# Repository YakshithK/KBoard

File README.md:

# KBoard

An 84-key custom mechanical keyboard built from scratch around the RP2040. No dev module: the RP2040, flash, regulator, USB-C, crystal, and support circuitry are all on the board. Uses Cherry MX Browns.

| Top | Bottom |
| --- | --- |
|  |  |

## Features
- 84 hot-swap MX-compatible switches in a ROW2COL matrix with per-key diodes
- From-scratch RP2040 design with USB-C, 16Mbit flash, and onboard 3.3V regulation
- QMK firmware with RP2040 USB bootloader (drag-and-drop UF2 flashing)

## Technical Details

The PCB is a basic 2-layer pcb (306 x 125 mm) using an RP2040 SoC with a USB-C connector. There's also a switch broken on the bottom for boot/reset.

## Bill of Materials

Please see: [`BOM.csv`](BOM.csv)

## Repo Index

### Start Here

| Path | Purpose |
| --- | --- |
| [`README.md`](README.md) | Project overview, features, bill of materials, and this repository map |
| [`BOM.csv`](BOM.csv) | Bill of materials |

### Hardware: KiCad

| Path | Purpose |
| --- | --- |
| [`kboard_pcb/KBoard.kicad_pro`](kboard_pcb/KBoard.kicad_pro) | KiCad project settings |
| [`kboard_pcb/KBoard.kicad_sch`](kboard_pcb/KBoard.kicad_sch) | Source schematic |
| [`kboard_pcb/KBoard.kicad_pcb`](kboard_pcb/KBoard.kicad_pcb) | Source PCB layout |

### Hardware: CAD Files

| Path | Purpose |
| --- | --- |
| [`CAD/KBoard.step`](CAD/KBoard.step) | 3D CAD model in STEP format |
| [`PCB/KBoard.step`](PCB/KBoard.step) | 3D CAD model in STEP format |
| [`PCB/KBoard.stl`](PCB/KBoard.stl) | 3D CAD model in STL format (local only, too large for git) |

### Hardware: Production Files

| Path | Purpose |
| --- | --- |
| [`production/KBoard-gerbers.zip`](production/KBoard-gerbers.zip) | Zipped Gerbers + drill, ready to upload to the fab |
| [`production/KBoard.step`](production/KBoard.step) | STEP model bundled for fabrication |
| [`production/gerbers/`](production/gerbers/) | Gerber plot, drill, and pick-and-place files |
| [`production/firmware/`](production/firmware/) | QMK firmware source and built UF2 for flashing |

### Hardware: Visual References

| Path | Purpose |
| --- | --- |
| [`assets/schematic.svg`](assets/schematic.svg) | Schematic preview |
| [`assets/pcb-top.png`](assets/pcb-top.png) | Top-side PCB render |
| [`assets/pcb-bottom.png`](assets/pcb-bottom.png) | Bottom-side PCB render |

### Firmware: QMK

| Path | Purpose |
| --- | --- |
| [`firmware/kboard/keyboard.json`](firmware/kboard/keyboard.json) | Keyboard identity, RP2040 target, pins, matrix, and layout |
| [`firmware/kboard/rules.mk`](firmware/kboard/rules.mk) | QMK build settings |
| [`firmware/kboard/config.h`](firmware/kboard/config.h) | Board configuration |
| [`firmware/kboard/kboard.h`](firmware/kboard/kboard.h) | Keyboard header included by QMK |
| [`firmware/kboard/keymaps/default/keymap.c`](firmware/kboard/keymaps/default/keymap.c) | Default keymap |

Build the firmware with `qmk compile -kb kboard -km default` (the `firmware/kboard` folder must be linked or copied to `qmk_firmware/keyboards/kboard`). Flash the resulting UF2, also bundled at [`production/firmware/kboard_default.uf2`](production/firmware/kboard_default.uf2), by double-pressing reset and dragging it onto the USB drive.

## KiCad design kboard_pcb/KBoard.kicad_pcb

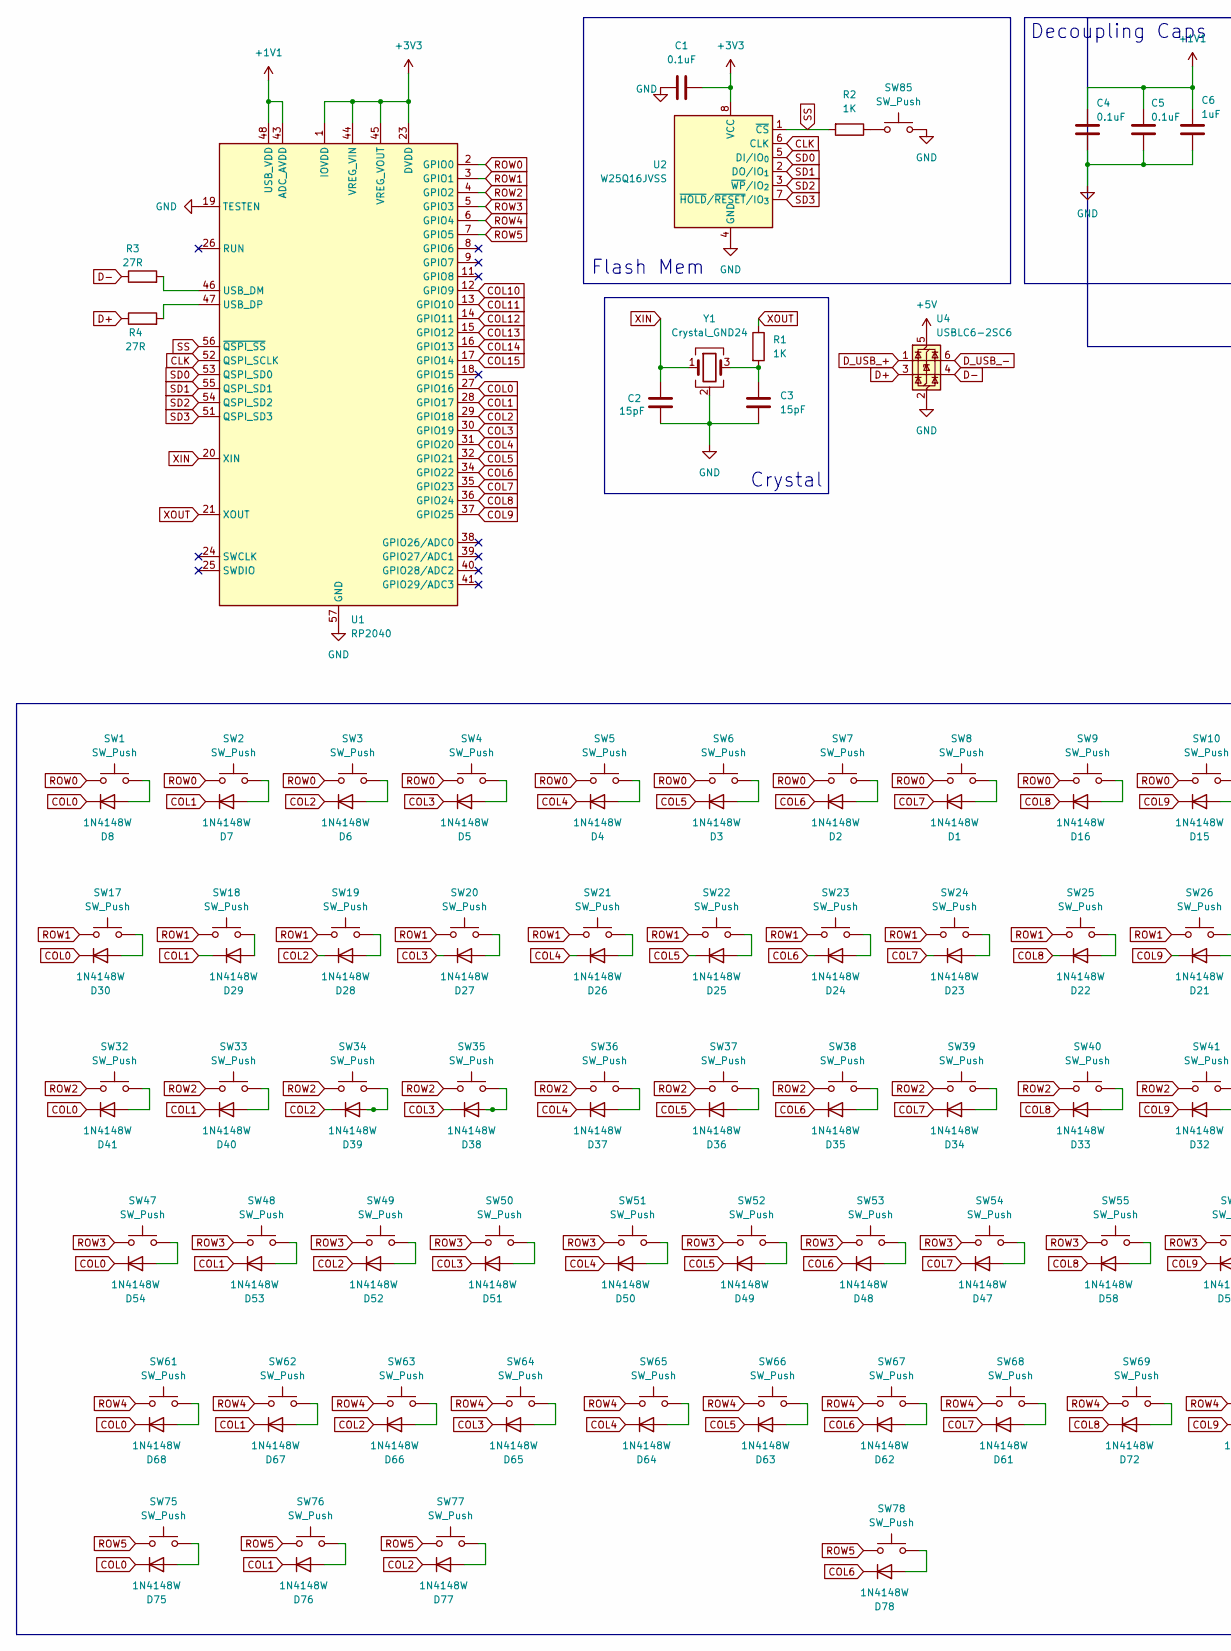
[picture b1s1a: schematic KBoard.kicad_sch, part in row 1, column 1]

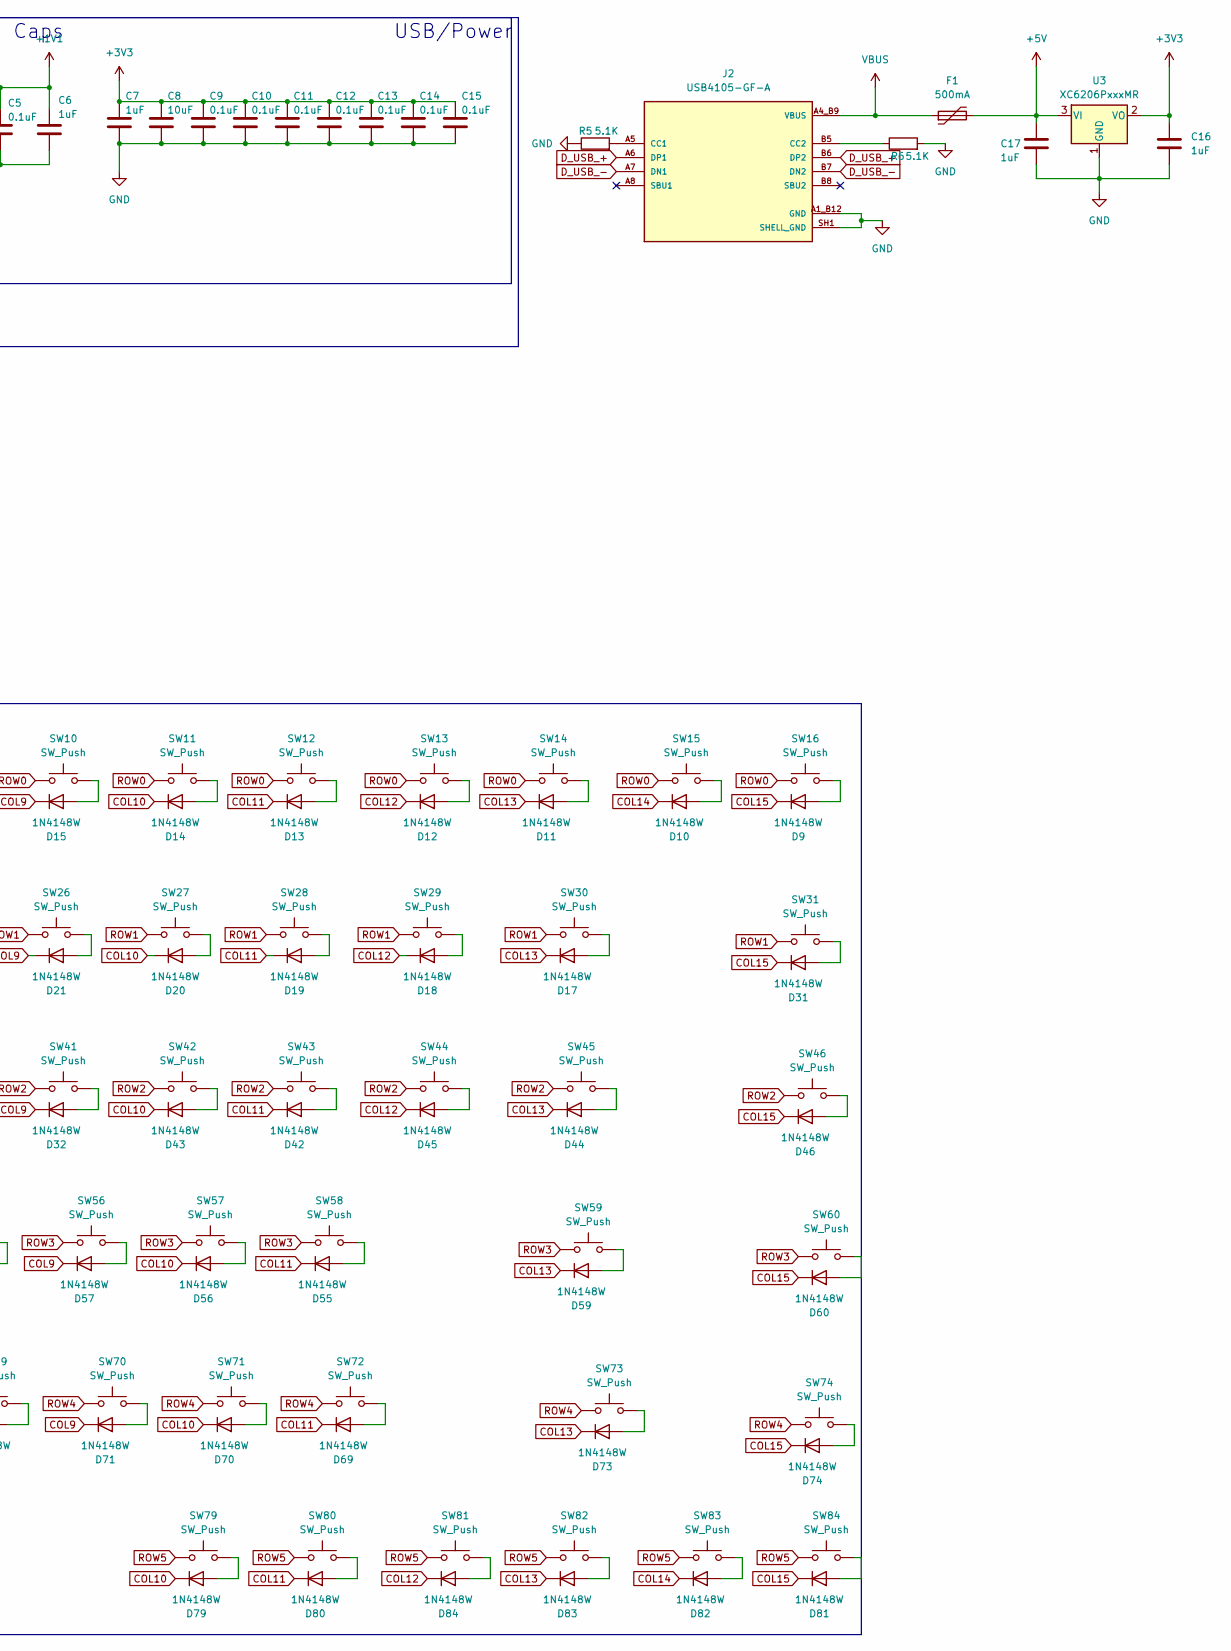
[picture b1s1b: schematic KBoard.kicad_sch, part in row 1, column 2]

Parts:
C1, C4, C5, C9, C10, C11, C12, C13, C14, C15: 0.1uF; C_0402_1005Metric
C2, C3: 15pF; C_0402_1005Metric
C6, C7, C16, C17: 1uF; C_0603_1608Metric
C8: 10uF; C_0603_1608Metric
D1, D2, D3, D4, D5, D6, D7, D8, D9, D10, D11, D12, D13, D14, D15, D16, D17, D18, D19, D20, D21, D22, D23, D24, D25, D26, D27, D28, D29, D30, D31, D32, D33, D34, D35, D36, D37, D38, D39, D40, D41, D42, D43, D44, D45, D46, D47, D48, D49, D50, D51, D52, D53, D54, D55, D56, D57, D58, D59, D60, D61, D62, D63, D64, D65, D66, D67, D68, D69, D70, D71, D72, D73, D74, D75, D76, D77, D78, D79, D80, D81, D82, D83, D84: 1N4148W; D_SOD-123
F1: 500mA; Fuse_0402_1005Metric
J2: USB4105-GF-A; GCT_USB4105-GF-A; PARTREV B4; DigiKey_Part_Number 2073-USB4105-GF-ACT-ND
R1, R2: 1K; C_0402_1005Metric
R3, R4: 27R; C_0402_1005Metric
R5, R6: 5.1K; C_0402_1005Metric
SW1, SW2, SW3, SW4, SW5, SW6, SW7, SW8, SW9, SW10, SW11, SW12, SW13, SW14, SW15, SW16, SW17, SW18, SW19, SW20, SW21, SW22, SW23, SW24, SW25, SW26, SW27, SW28, SW29, SW30, SW31, SW32, SW33, SW34, SW35, SW36, SW37, SW38, SW39, SW40, SW41, SW42, SW43, SW44, SW45, SW46, SW47, SW48, SW49, SW50, SW51, SW52, SW53, SW54, SW55, SW56, SW57, SW58, SW59, SW60, SW61, SW62, SW63, SW64, SW65, SW66, SW67, SW68, SW69, SW70, SW71, SW72, SW73, SW74, SW75, SW76, SW77, SW78, SW79, SW80, SW81, SW82, SW83, SW84: SW_Push; SW_MX_HS_CPG151101S11_1u
SW85: SW_Push; SW_SPST_CK_RS282G05A3
U1: RP2040; QFN-56-1EP_7x7mm_P0.4mm_EP3.2x3.2mm
U2: W25Q16JVSS; SOIC-8_5.3x5.3mm_P1.27mm
U3: XC6206PxxxMR; SOT-23-3
U4: USBLC6-2SC6; SOT-23-6
Y1: Crystal_GND24; Crystal_SMD_3225-4Pin_3.2x2.5mm

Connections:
+1V1: C4.1, C5.1, C6.1, U1.43 (ADC_AVDD), U1.48 (USB_VDD)
+3V3: C1.2, C7.1, C8.1, C9.1, C10.1, C11.1, C12.1, C13.1, C14.1, C15.1, C16.1, U1.1 (IOVDD), U1.10 (IOVDD), U1.22 (IOVDD), U1.23 (DVDD), U1.33 (IOVDD), U1.42 (IOVDD), U1.44 (VREG_VIN), U1.45 (VREG_VOUT), U1.49 (IOVDD), U1.50 (DVDD), U2.8 (VCC), U3.2 (VO)
+5V: C17.1, F1.2, U3.3 (VI), U4.5 (VBUS)
CLK: U1.52 (QSPI_SCLK), U2.6 (CLK)
COL0: D8.1 (K), D30.1 (K), D41.1 (K), D54.1 (K), D68.1 (K), D75.1 (K), U1.27 (GPIO16)
COL1: D7.1 (K), D29.1 (K), D40.1 (K), D53.1 (K), D67.1 (K), D76.1 (K), U1.28 (GPIO17)
COL2: D6.1 (K), D28.1 (K), D39.1 (K), D52.1 (K), D66.1 (K), D77.1 (K), U1.29 (GPIO18)
COL3: D5.1 (K), D27.1 (K), D38.1 (K), D51.1 (K), D65.1 (K), U1.30 (GPIO19)
COL4: D4.1 (K), D26.1 (K), D37.1 (K), D50.1 (K), D64.1 (K), U1.31 (GPIO20)
COL5: D3.1 (K), D25.1 (K), D36.1 (K), D49.1 (K), D63.1 (K), U1.32 (GPIO21)
COL6: D2.1 (K), D24.1 (K), D35.1 (K), D48.1 (K), D62.1 (K), D78.1 (K), U1.34 (GPIO22)
COL7: D1.1 (K), D23.1 (K), D34.1 (K), D47.1 (K), D61.1 (K), U1.35 (GPIO23)
COL8: D16.1 (K), D22.1 (K), D33.1 (K), D58.1 (K), D72.1 (K), U1.36 (GPIO24)
COL9: D15.1 (K), D21.1 (K), D32.1 (K), D57.1 (K), D71.1 (K), U1.37 (GPIO25)
COL10: D14.1 (K), D20.1 (K), D43.1 (K), D56.1 (K), D70.1 (K), D79.1 (K), U1.12 (GPIO9)
COL11: D13.1 (K), D19.1 (K), D42.1 (K), D55.1 (K), D69.1 (K), D80.1 (K), U1.13 (GPIO10)
COL12: D12.1 (K), D18.1 (K), D45.1 (K), D84.1 (K), U1.14 (GPIO11)
COL13: D11.1 (K), D17.1 (K), D44.1 (K), D59.1 (K), D73.1 (K), D83.1 (K), U1.15 (GPIO12)
COL14: D10.1 (K), D82.1 (K), U1.16 (GPIO13)
COL15: D9.1 (K), D31.1 (K), D46.1 (K), D60.1 (K), D74.1 (K), D81.1 (K), U1.17 (GPIO14)
D+: R4.1, U4.3 (I/O2)
D-: R3.1, U4.4 (I/O2)
D_USB_+: J2.A6 (DP1), J2.B6 (DP2), U4.1 (I/O1)
D_USB_-: J2.A7 (DN1), J2.B7 (DN2), U4.6 (I/O1)
GND: C1.1, C2.2, C3.2, C4.2, C5.2, C6.2, C7.2, C8.2, C9.2, C10.2, C11.2, C12.2, C13.2, C14.2, C15.2, C16.2, C17.2, J2.A1_B12 (GND), J2.B1_A12 (GND), J2.SH1 (SHELL_GND), J2.SH2 (SHELL_GND), J2.SH3 (SHELL_GND), J2.SH4 (SHELL_GND), R5.1, R6.2, SW85.2, U1.19 (TESTEN), U1.57 (GND), U2.4 (GND), U3.1 (GND), U4.2 (GND), Y1.2 (G), Y1.4 (G)
unnamed: C3.1, R1.2, Y1.3
unnamed: D1.2 (A), SW8.2
unnamed: D2.2 (A), SW7.2
unnamed: D3.2 (A), SW6.2
unnamed: D4.2 (A), SW5.2
unnamed: D5.2 (A), SW4.2
unnamed: D6.2 (A), SW3.2
unnamed: D7.2 (A), SW2.2
unnamed: D8.2 (A), SW1.2
unnamed: D9.2 (A), SW16.2
unnamed: D10.2 (A), SW15.2
unnamed: D11.2 (A), SW14.2
unnamed: D12.2 (A), SW13.2
unnamed: D13.2 (A), SW12.2
unnamed: D14.2 (A), SW11.2
unnamed: D15.2 (A), SW10.2
unnamed: D16.2 (A), SW9.2
unnamed: D17.2 (A), SW30.2
unnamed: D18.2 (A), SW29.2
unnamed: D19.2 (A), SW28.2
unnamed: D20.2 (A), SW27.2
unnamed: D21.2 (A), SW26.2
unnamed: D22.2 (A), SW25.2
unnamed: D23.2 (A), SW24.2
unnamed: D24.2 (A), SW23.2
unnamed: D25.2 (A), SW22.2
unnamed: D26.2 (A), SW21.2
unnamed: D27.2 (A), SW20.2
unnamed: D28.2 (A), SW19.2
unnamed: D29.2 (A), SW18.2
unnamed: D30.2 (A), SW17.2
unnamed: D31.2 (A), SW31.2
unnamed: D32.2 (A), SW41.2
unnamed: D33.2 (A), SW40.2
unnamed: D34.2 (A), SW39.2
unnamed: D35.2 (A), SW38.2
unnamed: D36.2 (A), SW37.2
unnamed: D37.2 (A), SW36.2
unnamed: D38.2 (A), SW35.2
unnamed: D39.2 (A), SW34.2
unnamed: D40.2 (A), SW33.2
unnamed: D41.2 (A), SW32.2
unnamed: D42.2 (A), SW43.2
unnamed: D43.2 (A), SW42.2
unnamed: D44.2 (A), SW45.2
unnamed: D45.2 (A), SW44.2
unnamed: D46.2 (A), SW46.2
unnamed: D47.2 (A), SW54.2
unnamed: D48.2 (A), SW53.2
unnamed: D49.2 (A), SW52.2
unnamed: D50.2 (A), SW51.2
unnamed: D51.2 (A), SW50.2
unnamed: D52.2 (A), SW49.2
unnamed: D53.2 (A), SW48.2
unnamed: D54.2 (A), SW47.2
unnamed: D55.2 (A), SW58.2
unnamed: D56.2 (A), SW57.2
unnamed: D57.2 (A), SW56.2
unnamed: D58.2 (A), SW55.2
unnamed: D59.2 (A), SW59.2
unnamed: D60.2 (A), SW60.2
unnamed: D61.2 (A), SW68.2
unnamed: D62.2 (A), SW67.2
unnamed: D63.2 (A), SW66.2
unnamed: D64.2 (A), SW65.2
unnamed: D65.2 (A), SW64.2
unnamed: D66.2 (A), SW63.2
unnamed: D67.2 (A), SW62.2
unnamed: D68.2 (A), SW61.2
unnamed: D69.2 (A), SW72.2
unnamed: D70.2 (A), SW71.2
unnamed: D71.2 (A), SW70.2
unnamed: D72.2 (A), SW69.2
unnamed: D73.2 (A), SW73.2
unnamed: D74.2 (A), SW74.2
unnamed: D75.2 (A), SW75.2
unnamed: D76.2 (A), SW76.2
unnamed: D77.2 (A), SW77.2
unnamed: D78.2 (A), SW78.2
unnamed: D79.2 (A), SW79.2
unnamed: D80.2 (A), SW80.2
unnamed: D81.2 (A), SW84.2
unnamed: D82.2 (A), SW83.2
unnamed: D83.2 (A), SW82.2
unnamed: D84.2 (A), SW81.2
unnamed: J2.A5 (CC1), R5.2
unnamed: J2.B5 (CC2), R6.1
unnamed: R2.1, SW85.1
unnamed: R3.2, U1.46 (USB_DM)
unnamed: R4.2, U1.47 (USB_DP)
ROW0: SW1.1, SW2.1, SW3.1, SW4.1, SW5.1, SW6.1, SW7.1, SW8.1, SW9.1, SW10.1, SW11.1, SW12.1, SW13.1, SW14.1, SW15.1, SW16.1, U1.2 (GPIO0)
ROW1: SW17.1, SW18.1, SW19.1, SW20.1, SW21.1, SW22.1, SW23.1, SW24.1, SW25.1, SW26.1, SW27.1, SW28.1, SW29.1, SW30.1, SW31.1, U1.3 (GPIO1)
ROW2: SW32.1, SW33.1, SW34.1, SW35.1, SW36.1, SW37.1, SW38.1, SW39.1, SW40.1, SW41.1, SW42.1, SW43.1, SW44.1, SW45.1, SW46.1, U1.4 (GPIO2)
ROW3: SW47.1, SW48.1, SW49.1, SW50.1, SW51.1, SW52.1, SW53.1, SW54.1, SW55.1, SW56.1, SW57.1, SW58.1, SW59.1, SW60.1, U1.5 (GPIO3)
ROW4: SW61.1, SW62.1, SW63.1, SW64.1, SW65.1, SW66.1, SW67.1, SW68.1, SW69.1, SW70.1, SW71.1, SW72.1, SW73.1, SW74.1, U1.6 (GPIO4)
ROW5: SW75.1, SW76.1, SW77.1, SW78.1, SW79.1, SW80.1, SW81.1, SW82.1, SW83.1, SW84.1, U1.7 (GPIO5)
SD0: U1.53 (QSPI_SD0), U2.5 (DI/IO_{0})
SD1: U1.55 (QSPI_SD1), U2.2 (DO/IO_{1})
SD2: U1.54 (QSPI_SD2), U2.3 (~WP/IO_{2})
SD3: U1.51 (QSPI_SD3), U2.7 (~HOLD/~RESET/IO_{3})
SS: R2.2, U1.56 (~QSPI_SS), U2.1 (~CS)
VBUS: F1.1, J2.A4_B9 (VBUS), J2.B4_A9 (VBUS)
XIN: C2.1, U1.20 (XIN), Y1.1
XOUT: R1.1, U1.21 (XOUT)

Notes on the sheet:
Crystal
Flash Mem
USB/Power
Decoupling Caps

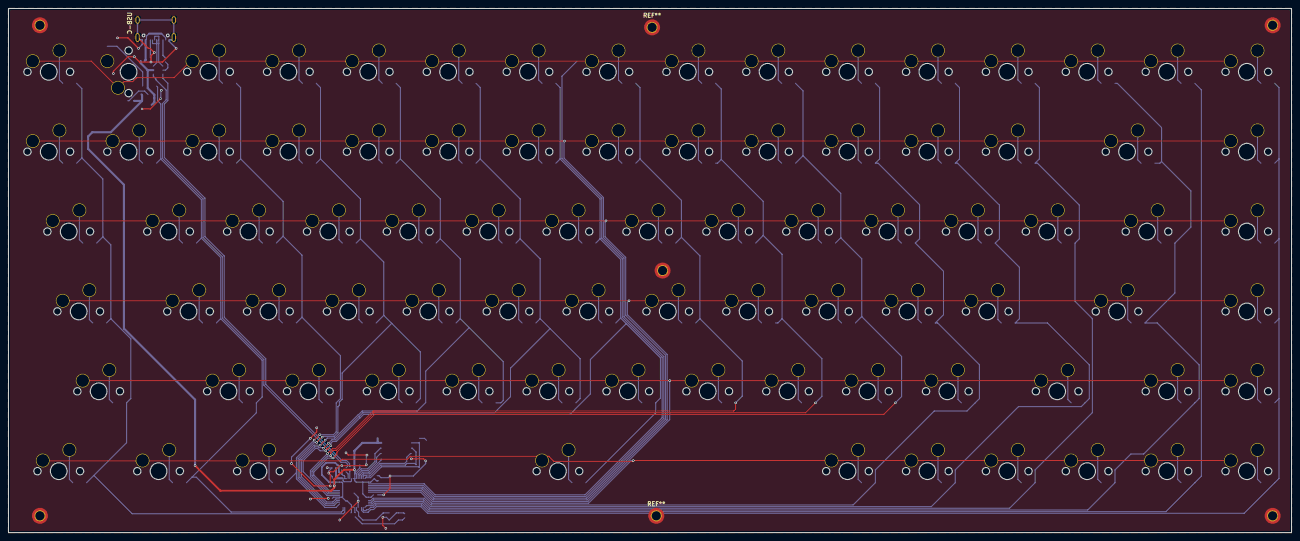
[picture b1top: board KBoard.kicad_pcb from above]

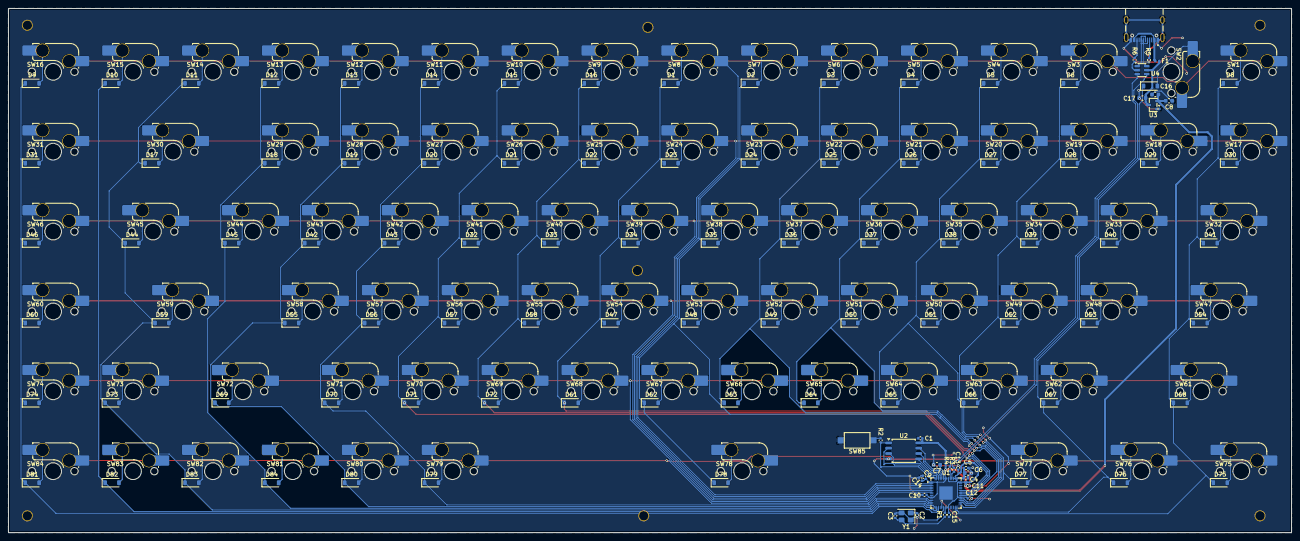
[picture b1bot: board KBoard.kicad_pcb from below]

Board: 2 copper layers, 306.0 x 125.0 mm, 199 parts (199 on the bottom side), 129 nets.

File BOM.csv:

Item,Reference,Quantity,Part,Description,Footprint,Notes
1,U1,1,RP2040,Raspberry Pi RP2040 microcontroller,Package_DFN_QFN:QFN-56-1EP_7x7mm_P0.4mm_EP3.2x3.2mm,
2,U2,1,W25Q16JVSS,16Mbit SPI flash memory,Package_SO:SOIC-8_5.3x5.3mm_P1.27mm,
3,U3,1,XC6206 3.3V,3.3V low-dropout linear regulator,Package_TO_SOT_SMD:SOT-23-3,
4,U4,1,USBLC6-2,USB ESD protection array,Package_TO_SOT_SMD:SOT-23-6,
5,Y1,1,12MHz crystal,SMD crystal for RP2040 clock (12MHz),Crystal:Crystal_SMD_3225-4Pin_3.2x2.5mm,
6,J2,1,USB4105-GF-A,USB Type-C 16-pin mid-mount receptacle,USB4105-GF-A:GCT_USB4105-GF-A,
7,F1,1,Polyfuse 500mA,Resettable fuse 0402,Fuse:Fuse_0402_1005Metric,
8,"R1, R2",2,Resistor 1k,0402 SMD resistor,Capacitor_SMD:C_0402_1005Metric,
9,"R3, R4",2,Resistor 27R,0402 SMD resistor (USB series termination),Capacitor_SMD:C_0402_1005Metric,
10,"R5, R6",2,Resistor 5.1k,0402 SMD resistor (USB-C CC pull-down),Capacitor_SMD:C_0402_1005Metric,
11,C1-C10,10,Capacitor 0.1uF,0402 MLCC decoupling capacitor,Capacitor_SMD:C_0402_1005Metric,
12,C11-C12,2,Capacitor 15pF,0402 MLCC crystal load capacitor,Capacitor_SMD:C_0402_1005Metric,
13,C13-C16,4,Capacitor 1uF,0603 MLCC capacitor,Capacitor_SMD:C_0603_1608Metric,
14,C17,1,Capacitor 10uF,0603 MLCC bulk capacitor,Capacitor_SMD:C_0603_1608Metric,
15,D1-D84,84,1N4148W,Fast switching diode for key matrix,Diode_SMD:D_SOD-123,
16,SW1-SW84,84,MX-style mechanical switch,Hot-swap MX compatible switch,PCM_marbastlib-mx:SW_MX_HS_CPG151101S11_1u,Any MX compatible switch works
17,SW85,1,Tactile switch,SMD tact switch (boot/reset),Button_Switch_SMD:SW_SPST_CK_RS282G05A3,
18,KC1-KC84,84,1u keycaps,Cherry MX profile keycaps,,
19,PCB1,1,KBoard PCB,2-layer KiCad PCB (306 x 125 mm),,"Order from JLCPCB, PCBWay, or similar"
